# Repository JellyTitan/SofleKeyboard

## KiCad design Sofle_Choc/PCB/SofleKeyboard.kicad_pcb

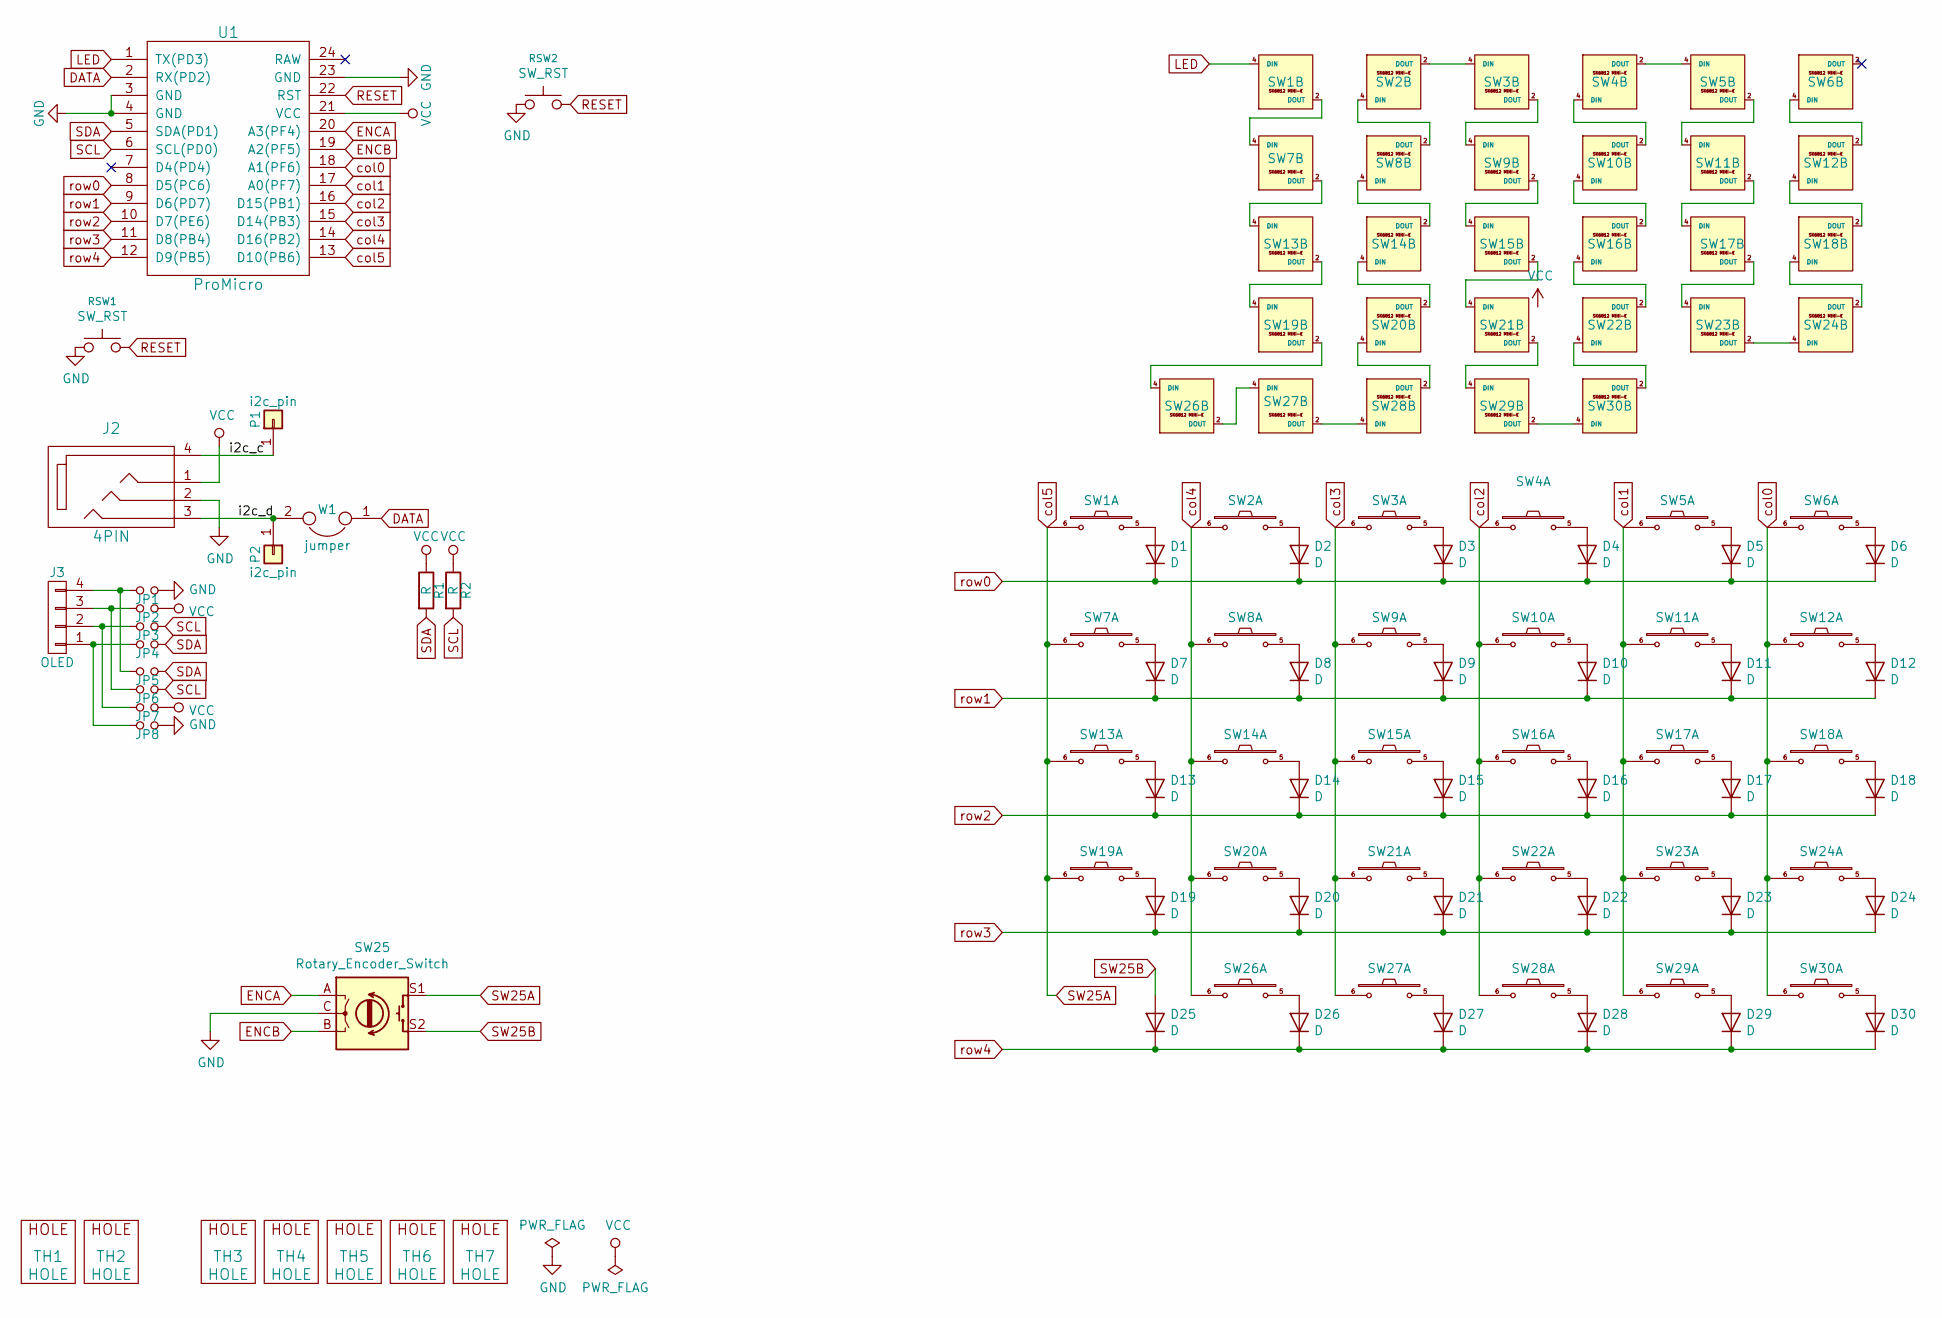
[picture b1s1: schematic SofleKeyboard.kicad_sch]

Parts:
D1, D2, D3, D4, D5, D6, D7, D8, D9, D10, D11, D12, D13, D14, D15, D16, D17, D18, D19, D20, D21, D22, D23, D24, D25, D26, D27, D28, D29, D30: D; crkbd-diode
J2: 4PIN; MJ-4PP-9
J3: OLED; OLED_4Pin
JP1, JP2, JP3, JP4, JP5, JP6, JP7, JP8: Jumper_NO_Small; Jumper
P1, P2: i2c_pin; 1pin_conn
R1, R2: R; RESISTOR_mini
RSW1, RSW2: SW_RST; TACT_SWITCH_TVBP06
SW1, SW2, SW3, SW4, SW5, SW6, SW7, SW8, SW9, SW10, SW11, SW12, SW13, SW14, SW15, SW16, SW17, SW18, SW19, SW20, SW21, SW22, SW23, SW24, SW26, SW27, SW28, SW29, SW30: SW_PUSH_LED; Choc_Hotswap_SK6812MiniE
SW25: Rotary_Encoder_Switch; RotaryEncoder_Alps_EC11E-Switch_Vertical_H20mm-keebio_modif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
TH1, TH2: HOLE; M2_HOLE_PCB
TH3, TH4, TH5, TH6, TH7: HOLE; HOLE_M2_TH
U1: ProMicro
W1: jumper; jumper_data

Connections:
/i2c_c: J2.4, P1.1
/i2c_d: J2.3, P2.1, W1.2
DATA: U1.2 (RX(PD2)), W1.1
ENCA: SW25.A, U1.20 (A3(PF4))
ENCB: SW25.B, U1.19 (A2(PF5))
GND: J2.2, JP1.2, JP8.2, RSW1.1, SW1.3 (GND), SW2.3 (GND), SW3.3 (GND), SW4.3 (GND), SW5.3 (GND), SW6.3 (GND), SW7.3 (GND), SW8.3 (GND), SW9.3 (GND), SW10.3 (GND), SW11.3 (GND), SW12.3 (GND), SW13.3 (GND), SW14.3 (GND), SW15.3 (GND), SW16.3 (GND), SW17.3 (GND), SW18.3 (GND), SW19.3 (GND), SW20.3 (GND), SW21.3 (GND), SW22.3 (GND), SW23.3 (GND), SW24.3 (GND), SW25.C, SW26.3 (GND), SW27.3 (GND), SW28.3 (GND), SW29.3 (GND), SW30.3 (GND), U1.3 (GND), U1.4 (GND), U1.23 (GND)
LED: SW1.4 (DIN), U1.1 (TX(PD3))
unnamed: D1.2 (A), SW1.5
unnamed: D2.2 (A), SW2.5
unnamed: D3.2 (A), SW3.5
unnamed: D4.2 (A), SW4.5
unnamed: D5.2 (A), SW5.5
unnamed: D6.2 (A), SW6.5
unnamed: D7.2 (A), SW7.5
unnamed: D8.2 (A), SW8.5
unnamed: D9.2 (A), SW9.5
unnamed: D10.2 (A), SW10.5
unnamed: D11.2 (A), SW11.5
unnamed: D12.2 (A), SW12.5
unnamed: D13.2 (A), SW13.5
unnamed: D14.2 (A), SW14.5
unnamed: D15.2 (A), SW15.5
unnamed: D16.2 (A), SW16.5
unnamed: D17.2 (A), SW17.5
unnamed: D18.2 (A), SW18.5
unnamed: D19.2 (A), SW19.5
unnamed: D20.2 (A), SW20.5
unnamed: D21.2 (A), SW21.5
unnamed: D22.2 (A), SW22.5
unnamed: D23.2 (A), SW23.5
unnamed: D24.2 (A), SW24.5
unnamed: D26.2 (A), SW26.5
unnamed: D27.2 (A), SW27.5
unnamed: D28.2 (A), SW28.5
unnamed: D29.2 (A), SW29.5
unnamed: D30.2 (A), SW30.5
unnamed: J3.1, JP4.1, JP8.1
unnamed: J3.2, JP3.1, JP7.1
unnamed: J3.3, JP2.1, JP6.1
unnamed: J3.4, JP1.1, JP5.1
unnamed: SW1.2 (DOUT), SW7.4 (DIN)
unnamed: SW2.2 (DOUT), SW3.4 (DIN)
unnamed: SW2.4 (DIN), SW8.2 (DOUT)
unnamed: SW3.2 (DOUT), SW9.4 (DIN)
unnamed: SW4.2 (DOUT), SW5.4 (DIN)
unnamed: SW4.4 (DIN), SW10.2 (DOUT)
unnamed: SW10.4 (DIN), SW16.2 (DOUT)
unnamed: SW11.2 (DOUT), SW17.4 (DIN)
unnamed: SW5.2 (DOUT), SW11.4 (DIN)
unnamed: SW6.4 (DIN), SW12.2 (DOUT)
unnamed: SW12.4 (DIN), SW18.2 (DOUT)
unnamed: SW13.2 (DOUT), SW19.4 (DIN)
unnamed: SW7.2 (DOUT), SW13.4 (DIN)
unnamed: SW8.4 (DIN), SW14.2 (DOUT)
unnamed: SW14.4 (DIN), SW20.2 (DOUT)
unnamed: SW15.2 (DOUT), SW21.4 (DIN)
unnamed: SW9.2 (DOUT), SW15.4 (DIN)
unnamed: SW16.4 (DIN), SW22.2 (DOUT)
unnamed: SW17.2 (DOUT), SW23.4 (DIN)
unnamed: SW18.4 (DIN), SW24.2 (DOUT)
unnamed: SW19.2 (DOUT), SW26.4 (DIN)
unnamed: SW20.4 (DIN), SW28.2 (DOUT)
unnamed: SW21.2 (DOUT), SW29.4 (DIN)
unnamed: SW22.4 (DIN), SW30.2 (DOUT)
unnamed: SW23.2 (DOUT), SW24.4 (DIN)
unnamed: SW26.2 (DOUT), SW27.4 (DIN)
unnamed: SW27.2 (DOUT), SW28.4 (DIN)
unnamed: SW29.2 (DOUT), SW30.4 (DIN)
RESET: RSW1.2, U1.22 (RST)
SCL: JP3.2, JP6.2, R2.2, U1.6 (SCL(PD0))
SDA: JP4.2, JP5.2, R1.2, U1.5 (SDA(PD1))
SW25A: SW1.6, SW7.6, SW13.6, SW19.6, SW25.S1, U1.13 (D10(PB6))
SW25B: D25.2 (A), SW25.S2
VCC: J2.1, JP2.2, JP7.2, R1.1, R2.1, SW1.1 (VDD), SW2.1 (VDD), SW3.1 (VDD), SW4.1 (VDD), SW5.1 (VDD), SW6.1 (VDD), SW7.1 (VDD), SW8.1 (VDD), SW9.1 (VDD), SW10.1 (VDD), SW11.1 (VDD), SW12.1 (VDD), SW13.1 (VDD), SW14.1 (VDD), SW15.1 (VDD), SW16.1 (VDD), SW17.1 (VDD), SW18.1 (VDD), SW19.1 (VDD), SW20.1 (VDD), SW21.1 (VDD), SW22.1 (VDD), SW23.1 (VDD), SW24.1 (VDD), SW26.1 (VDD), SW27.1 (VDD), SW28.1 (VDD), SW29.1 (VDD), SW30.1 (VDD), U1.21 (VCC)
col0: SW6.6, SW12.6, SW18.6, SW24.6, SW30.6, U1.18 (A1(PF6))
col1: SW5.6, SW11.6, SW17.6, SW23.6, SW29.6, U1.17 (A0(PF7))
col2: SW4.6, SW10.6, SW16.6, SW22.6, SW28.6, U1.16 (D15(PB1))
col3: SW3.6, SW9.6, SW15.6, SW21.6, SW27.6, U1.15 (D14(PB3))
col4: SW2.6, SW8.6, SW14.6, SW20.6, SW26.6, U1.14 (D16(PB2))
row0: D1.1 (K), D2.1 (K), D3.1 (K), D4.1 (K), D5.1 (K), D6.1 (K), U1.8 (D5(PC6))
row1: D7.1 (K), D8.1 (K), D9.1 (K), D10.1 (K), D11.1 (K), D12.1 (K), U1.9 (D6(PD7))
row2: D13.1 (K), D14.1 (K), D15.1 (K), D16.1 (K), D17.1 (K), D18.1 (K), U1.10 (D7(PE6))
row3: D19.1 (K), D20.1 (K), D21.1 (K), D22.1 (K), D23.1 (K), D24.1 (K), U1.11 (D8(PB4))
row4: D25.1 (K), D26.1 (K), D27.1 (K), D28.1 (K), D29.1 (K), D30.1 (K), U1.12 (D9(PB5))

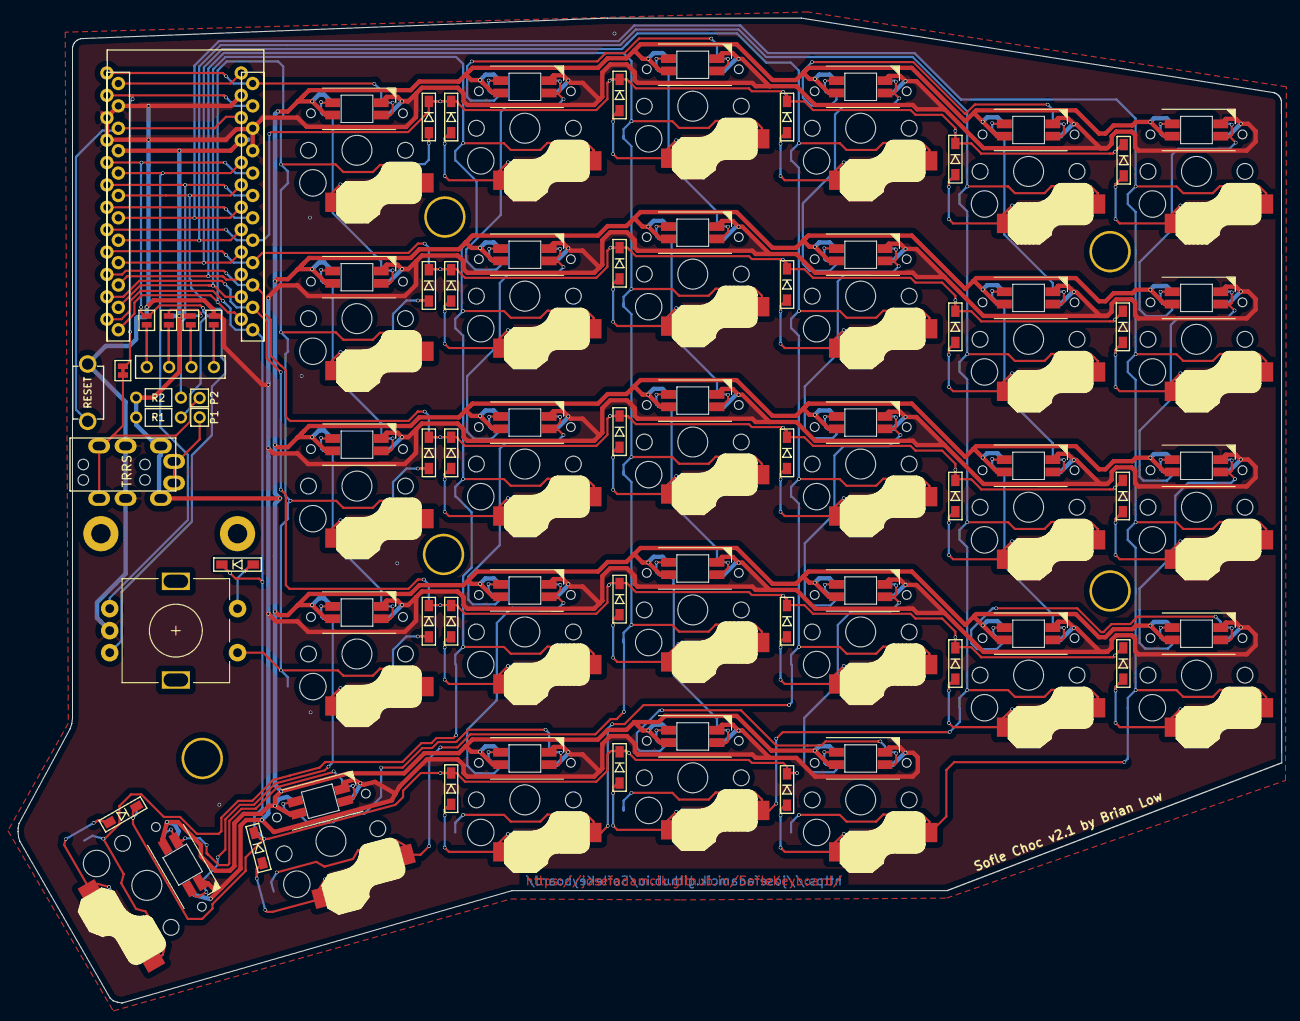
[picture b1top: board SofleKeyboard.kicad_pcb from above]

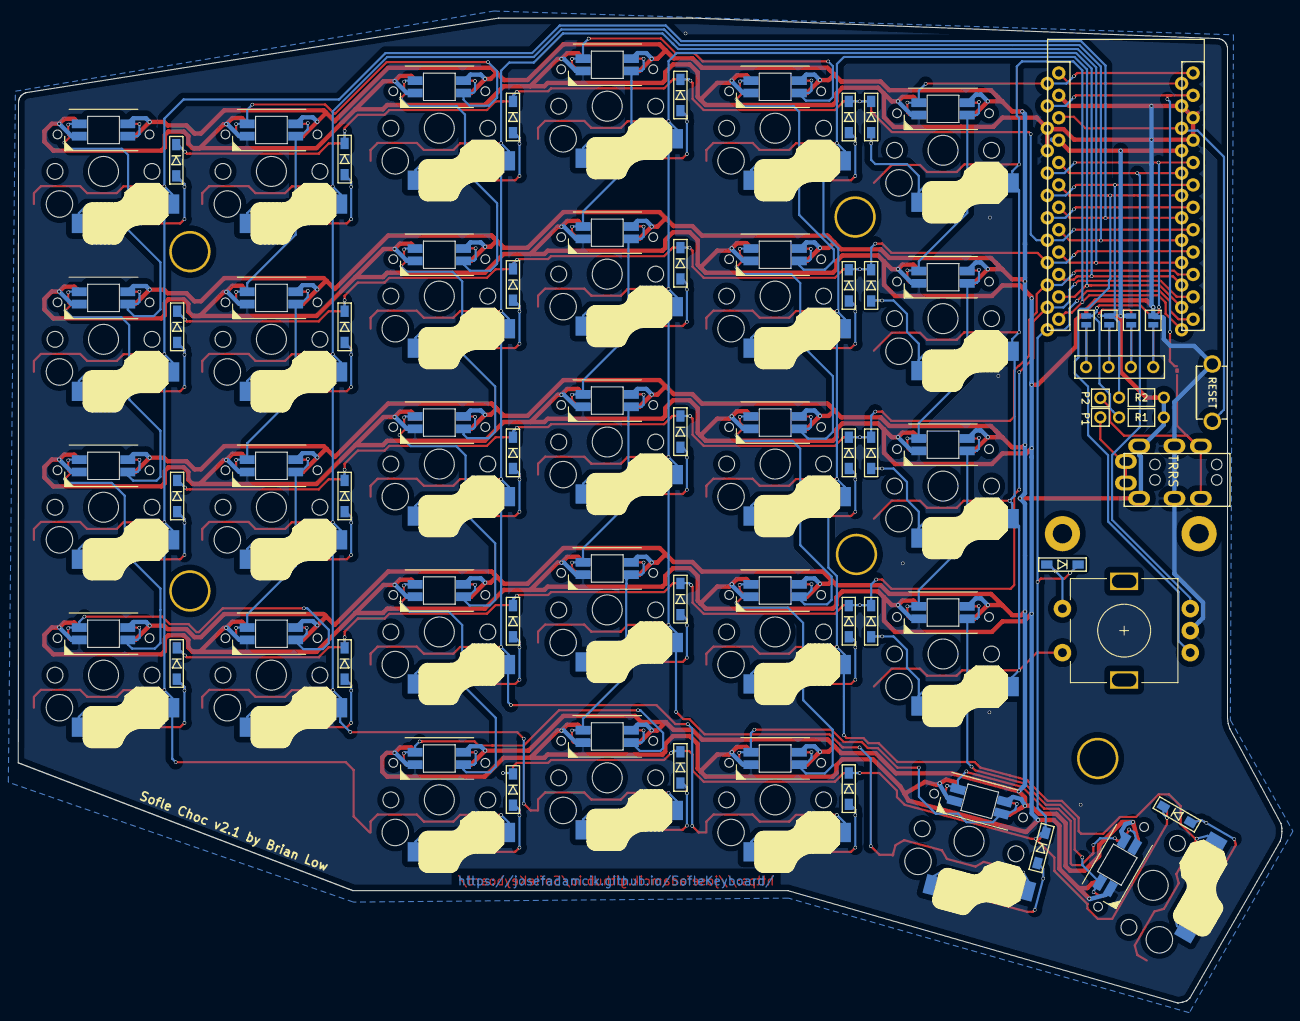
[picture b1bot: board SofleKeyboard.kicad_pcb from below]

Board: 2 copper layers, 143.4 x 111.8 mm, 84 parts (4 on the bottom side), 84 nets.

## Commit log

2023-03-18 Cloned ChocV2 MX variant from sofle choc Replaced Choc V1 footprints with Choc V2 footprints
2023-03-18 Tied front zone to VCC Updated LED footprint with compact DS variant
2023-03-18 Swapped out SMD Diode footprint for through-hole SMD hybrid footprint
2023-03-18 Wiped switch vias and traces for reroute
2023-03-18 Diodes moved to prevent footprint overlaps
2023-03-19 Switch footprint overhaul switch rerouteing
2023-03-19 More routing
2023-03-19 Updated attribution text
2023-03-19 Reworked thumb cluster for simplicity
2023-03-19 Key 19 Rebuild and DRC cleanup
2023-03-20 Switch footprint rework for consistent clearance
2023-03-20 Hole size tweaks for JLCPCB and DRC
2023-03-20 ProMicro footprint variant created backside shifted .25 -x to resolve DRC clearance violations
2023-03-20 Created TRRS footprint variant Poka-yoke by removing unnecessary trrs masks
2023-03-20 Added teardrops
2023-03-20 Revised mini-e footprint for elegant routing
2023-03-21 Sent this version out for production at jlcpcb
2023-03-21 Started build guide
2023-03-21 Added double OLED footprint and removed jumpers
2023-03-23 OLED second socket added Updated schematic to remove jumpers for DS oled socket Increased Promicro footrprint spacing Cleaned up promicro routing Simplified promicro footprint for poke-yoke soldering
2023-03-24 Removed reset button added poke-yoke reset graphics Tweaked I2C component location
2023-03-25 Fixed I2C bus rerouted and cleaned up teardrops labeleing tweaks DRC
2023-03-25 Moved TRRS jack and screen cover mounting hole to fix conflict with Pimoroni mounting holes
2023-03-26 Tweaked OLED footprint
2023-03-27 Added diode bender
2023-03-28 Reworked outline for consistent .5 offset and standardized corner angles
2023-03-28 Rotated 1.25u thumb key by 3deg Moved thumb key ~1mm left and down to resolve MX key overlap when using 1.25u keycaps
2023-03-31 Build guide cleanup (wip)
2023-03-31 Removed unused B.Silkscreen jlcpcb order number
2023-03-31 Enlarged choc v2 3rd pin hole
2023-03-31 Enlarged hotswap pads for easier soldering
2023-03-31 Reduced diode diameter from 1.2 to .9
2023-04-02 Added larger mini-e ground pin markings The small ground pin markings were obscured during sm soldering Added note about origin of choc V2 footprint from Foostan kbd library
2023-04-03 Right aligned all diodes and rerouted
2023-04-05 Consolidated I2C Components into one area
2023-04-05 Aligned thumb diodes for easier debugbugging
2023-04-05 Rally stripes added thumb diode placement tweak
2023-04-05 Gerber regen and doc update
2023-04-06 Library cleanup and consolidation
2023-04-06 Converted i2c jumper pads to through hole and moved diodes
2023-04-08 'Sofle loud' first commit
2023-04-08 Updated transistor footprint Added extra room for heatsink Rebuilt outline Wired solenoid and piezzo
2023-04-08 Footprint cleanup for plates Added markings to OLEDs indicating screen start/end offset oleds 3mm from edge of board rotated transistor for more slop on heatsinks Created Double sided TRRS footprint 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
2023-04-09 Adding 2nd tier keyplate
2023-04-10 SENT THIS VERSION OUT FOR PRODUCTION created key plates created top plates above key plates tweaked component layout to make room for plate M2 f-f spacers
2023-04-10 Generated bottom plate did not send out for production yet
2023-04-10 Added CKBD submodule wired up 3d model path for KDB submodule Updated TRRS 3d model Updated TRRS footprint masks
2023-04-16 Checkpoint commit Sent the backplate out for production
2023-04-23 Added 3d models
2023-04-23 Improved diode labeling Improved switch labeling increased diode labeling size for better visibility Added 3d models
2023-04-23 Updated pimoroni markings Added 3d models to components
2023-04-23 Created 3d models from case plates
2023-04-24 Improved tip120 pcb markings
2023-04-24 Added extra plates to 3d model
2023-04-25 Silkscreen mcu tweaks
2023-04-26 Fixed reveresed OLED pins
2023-05-01 Checkpoint commit
2023-05-02 Fixed TRRS markings Switched oled footprint so it's consistent distance from TRRS
2023-05-07 Added tenting puck holes
2023-05-07 Revised Main board outline Solenoid should now attach to bottom plate Removed speaker Rerouted for new plate cutouts
2023-05-07 Updated docs
2023-05-23 Updated with lessons learned from prototype build
2024-02-17 Fixed _blank liks in build guide
2024-03-03 First pass at comparison graphics Revised all keyboards to use outline stubbs Generated nested SVG's and color pallete
2024-03-03 Adds favicon
2024-03-04 Adds favicon code to head Adds favicon and image files
2024-03-05 Moved compare tool to _includes moved source vectors to design folder
2024-03-05 Added default check state and opacity to compare include
